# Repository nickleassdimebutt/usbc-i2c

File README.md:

# usbc-i2c

USB-C powered I²C breakout — 5 V in, 3.3 V out, 10 kΩ SDA/SCL pullups,
4-pin header to chain sensors. Power-good LED (green) on +3V3.

PCBA-2 test project for the [kicad-claude-toolkit](https://github.com/nickleassdimebutt/kicad-claude-toolkit)
v3 toolchain. Tighter layout than usbc-charger (14 components vs 23) so
hand-routed tracks could go DRC-clean for the routing that *does* exist.

## Layout status

The validated routes from usbc-3v3 (J1 escape, VBUS bus, CC pulldowns,
GND bridges) are reused verbatim. The new fan-out (+3V3 to LDO output
caps, the I²C pullups, the LED, the 4-pin user header) is left for
KiCad GUI hand-routing — same reason as usbc-charger: code-only routing
without a visual feedback loop accumulates pad-coordinate errors very
quickly.

DRC reports:

- 10 unconnected items — every +3V3 / SDA / SCL / N_D1 stub (expected,
  routing TODO)
- 1 dangling track — leftover endpoint from a stub I trimmed
- 4 cosmetic silk warnings (overlap, edge clearance, copper clip) — all
  non-fatal, would be silenced via project rule overrides

The board is **topologically correct** (`circuit.py` builds, BOM is
clean, schematic SVG renders) and the full datasheet pipeline runs
end-to-end on it.

## Build

```powershell
& "C:\Program Files\KiCad\10.0\bin\python.exe" build.py --datasheet --sim
```

## Topology summary

| Block | Components | Function |
|-------|------------|----------|
| `usbc_power` | J1 + R1, R2 | USB-C 5 V input + CC pulldowns |
| `ldo` | U1 + C1, C2, C3 | AMS1117-3.3 LDO with bypass caps |
| `i2c_pullups` | R10, R11 | 10 kΩ SDA / SCL pullups to +3V3 |
| `led` | D1 + R3 | Green +3V3 power-good indicator |
| `header` | J2 | 4-pin I²C user header (3V3/GND/SDA/SCL) |
| `mounting` | H1, H2 | Two M2 corner holes |

14 components, 8 nets, 50 × 30 mm.

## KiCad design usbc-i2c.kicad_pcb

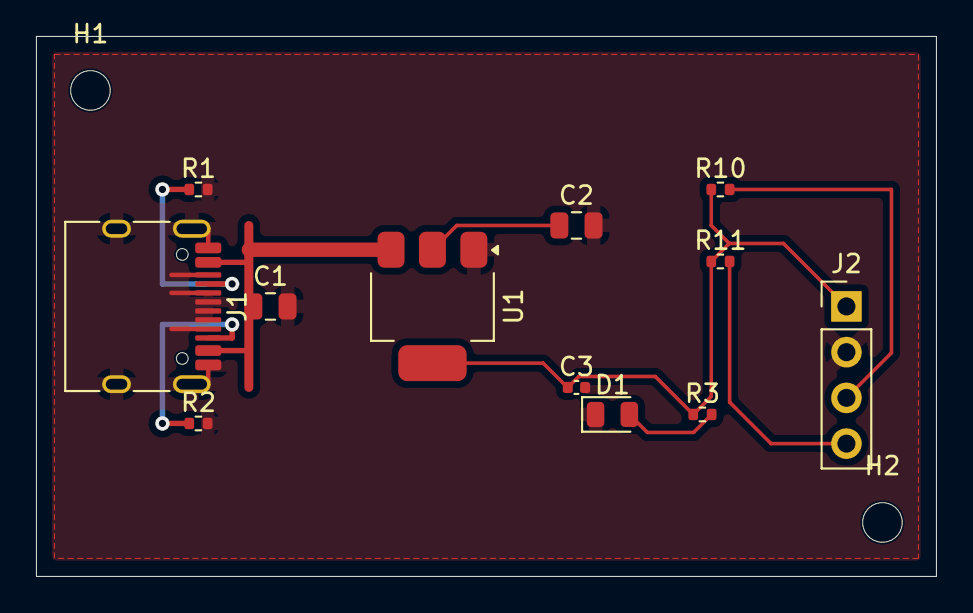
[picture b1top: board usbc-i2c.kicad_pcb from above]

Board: 2 copper layers, 50.0 x 30.0 mm, 14 parts (0 on the bottom side), 8 nets.

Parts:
C1, C2: 10uF; C_0805_2012Metric
C3: 100nF; C_0402_1005Metric
D1: GREEN; LED_0805_2012Metric
H1, H2: MountingHole_M2; MountingHole_2.2mm_M2
J1: HRO TYPE-C-31-M-12; USB_C_Receptacle_HRO_TYPE-C-31-M-12
J2: I2C; PinHeader_1x04_P2.54mm_Vertical
R1, R2: 5.1k; R_0402_1005Metric
R3: 820.0; R_0402_1005Metric
R10, R11: 10k; R_0402_1005Metric
U1: AMS1117-3.3; SOT-223-3_TabPin2

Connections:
+3V3: C2.1, C3.1, J2.1, R3.1, R10.1, R11.1, U1.2
CC1: J1.A5, R1.1
CC2: J1.B5, R2.1
GND: C1.2, C2.2, C3.2, D1.1, J1.A1, J1.A6, J1.A7, J1.A8, J1.A12, J1.B1, J1.B6, J1.B7, J1.B8, J1.B12, J1.SH, J2.2, R1.2, R2.2, U1.1
N_D1: D1.2, R3.2
SCL: J2.4, R11.2
SDA: J2.3, R10.2
VBUS: C1.1, J1.A4, J1.A9, J1.B4, J1.B9, U1.3
